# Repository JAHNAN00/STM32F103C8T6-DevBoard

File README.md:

# STM32F103C8T6-DevBoard

A dev board of STM32F103C8T6. Finished by Kicad.

Based on STM32F103C8T6-LQFP48,with type-C USB connector,8MHz and 32.768kHz crystal. Use AMS1117-3.3V as LDO.

Just for practice.

## Schematic

## PCB

## Image

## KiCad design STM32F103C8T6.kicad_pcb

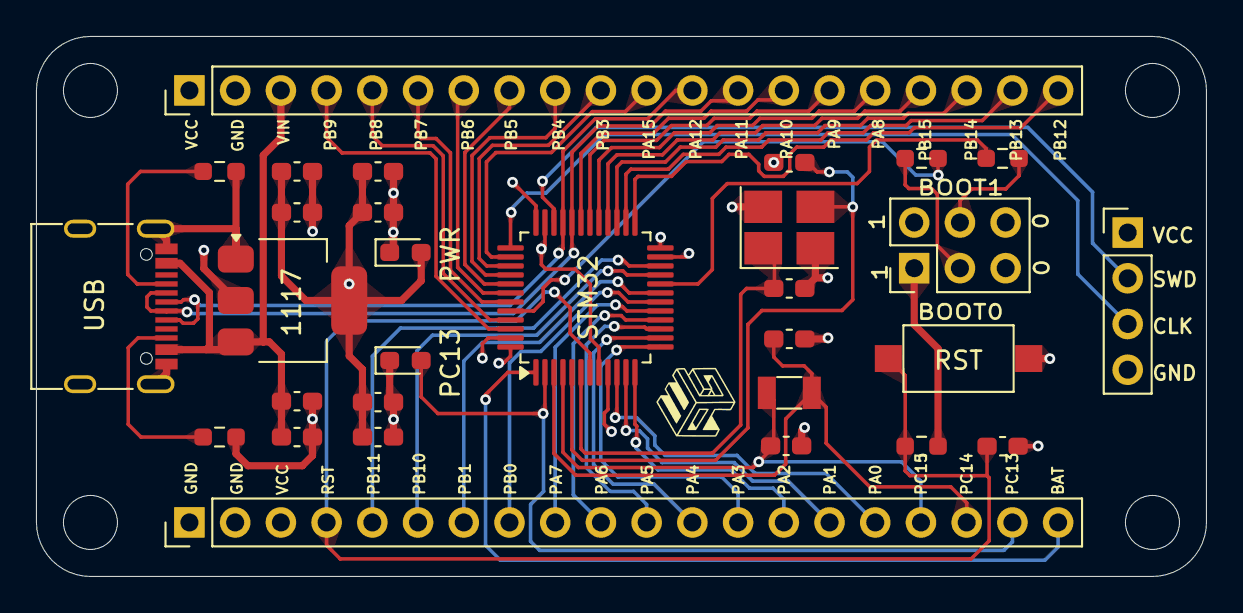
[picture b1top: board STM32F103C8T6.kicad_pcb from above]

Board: 4 copper layers, 65.0 x 30.0 mm, 30 parts (0 on the bottom side), 47 nets.

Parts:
1117: AMS1117-3.3; SOT-223-3_TabPin2
BOOT0: Conn_02x03_Odd_Even; PinHeader_2x03_P2.54mm_Vertical
C1, C4, C9: 1uF; C_0603_1608Metric_Pad1.08x0.95mm_HandSolder
C2, C3, C5, C6, C7, C8: 100nF; C_0603_1608Metric_Pad1.08x0.95mm_HandSolder
C10, C11, C12, C13: 20pF; C_0603_1608Metric_Pad1.08x0.95mm_HandSolder
J3: Conn_01x04; PinHeader_1x04_P2.54mm_Vertical
J4, J5: Conn_01x20; PinHeader_1x20_P2.54mm_Vertical
PC13: LED; LED_0603_1608Metric_Pad1.05x0.95mm_HandSolder
PWR: LED; LED_0603_1608Metric_Pad1.05x0.95mm_HandSolder
R1, R3: 5.1K; R_0603_1608Metric_Pad0.98x0.95mm_HandSolder
R2: 5.1k; R_0603_1608Metric_Pad0.98x0.95mm_HandSolder
R4, R5: 10K; R_0603_1608Metric_Pad0.98x0.95mm_HandSolder
RST: SW_Push; SW_SPST_CK_RS282G05A3
STM32: STM32F103C8Tx; LQFP-48_7x7mm_P0.5mm
USB: USB_C_Receptacle_USB2.0_16P; USB_C_Receptacle_G-Switch_GT-USB-7010ASV
Y1: 32.768kHz; Crystal_SMD_3215-2Pin_3.2x1.5mm
Y2: 8MHz; Crystal_SMD_3225-4Pin_3.2x2.5mm_HandSoldering

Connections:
+5V: 1117.3 (VI), C1.1, C2.1, J5.3, USB.A4 (VBUS), USB.A9 (VBUS), USB.B4 (VBUS), USB.B9 (VBUS)
BOOT0: R4.2, STM32.44 (BOOT0)
BOOT1: R5.1, STM32.20 (PB2)
D+: J5.12, STM32.33 (PA12), USB.A6 (D+), USB.B6 (D+)
D-: J5.13, STM32.32 (PA11), USB.A7 (D-), USB.B7 (D-)
GND: 1117.1 (GND), BOOT0.5, BOOT0.6, C1.2, C2.2, C3.2, C4.2, C5.2, C6.2, C7.2, C8.2, C9.2, C10.1, C11.2, C12.2, C13.2, J3.4, J4.1, J4.2, J5.2, PC13.1 (K), PWR.1 (K), R1.2, R2.2, RST.1, STM32.8 (VSSA), STM32.23 (VSS), STM32.35 (VSS), STM32.47 (VSS), USB.A1 (GND), USB.A12 (GND), USB.B1 (GND), USB.B12 (GND), USB.S1 (SHIELD), Y2.2, Y2.4
NRST: C9.1, J4.4, R3.1, RST.2, STM32.7 (NRST)
unnamed: R1.1, USB.A5 (CC1)
unnamed: R2.1, USB.B5 (CC2)
unnamed: BOOT0.3, R4.1
unnamed: BOOT0.4, R5.2
OSC32_IN: C13.1, J4.18, STM32.3 (PC14), Y1.2
OSC32_OUT: C12.1, J4.17, STM32.4 (PC15), Y1.1
OSC_IN: C10.2, STM32.5 (PD0), Y2.3
OSC_OUT: C11.1, STM32.6 (PD1), Y2.1
PA0: J4.16, STM32.10 (PA0)
PA1: J4.15, STM32.11 (PA1)
PA2: J4.14, STM32.12 (PA2)
PA3: J4.13, STM32.13 (PA3)
PA4: J4.12, STM32.14 (PA4)
PA5: J4.11, STM32.15 (PA5)
PA6: J4.10, STM32.16 (PA6)
PA7: J4.9, STM32.17 (PA7)
PA8: J5.16, STM32.29 (PA8)
PA9: J5.15, STM32.30 (PA9)
PA10: J5.14, STM32.31 (PA10)
PA15: J5.11, STM32.38 (PA15)
PB0: J4.8, STM32.18 (PB0)
PB1: J4.7, STM32.19 (PB1)
PB3: J5.10, STM32.39 (PB3)
PB4: J5.9, STM32.40 (PB4)
PB5: J5.8, STM32.41 (PB5)
PB6: J5.7, STM32.42 (PB6)
PB7: J5.6, STM32.43 (PB7)
PB8: J5.5, STM32.45 (PB8)
PB9: J5.4, STM32.46 (PB9)
PB10: J4.6, STM32.21 (PB10)
PB11: J4.5, STM32.22 (PB11)
PB12: J5.20, STM32.25 (PB12)
PB13: J5.19, STM32.26 (PB13)
PB14: J5.18, STM32.27 (PB14)
PB15: J5.17, STM32.28 (PB15)
PC13: J4.19, PC13.2 (A), STM32.2 (PC13)
SWCLK: J3.3, STM32.37 (PA14)
SWDIO: J3.2, STM32.34 (PA13)
VCC: 1117.2 (VO), BOOT0.1, BOOT0.2, C3.1, C4.1, C5.1, C6.1, C7.1, C8.1, J3.1, J4.3, J5.1, PWR.2 (A), R3.2, STM32.9 (VDDA), STM32.24 (VDD), STM32.36 (VDD), STM32.48 (VDD)
VDC: J4.20, STM32.1 (VBAT)

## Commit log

2024-10-18 Add silk screen,changed some cap
2024-10-18 edited readme
